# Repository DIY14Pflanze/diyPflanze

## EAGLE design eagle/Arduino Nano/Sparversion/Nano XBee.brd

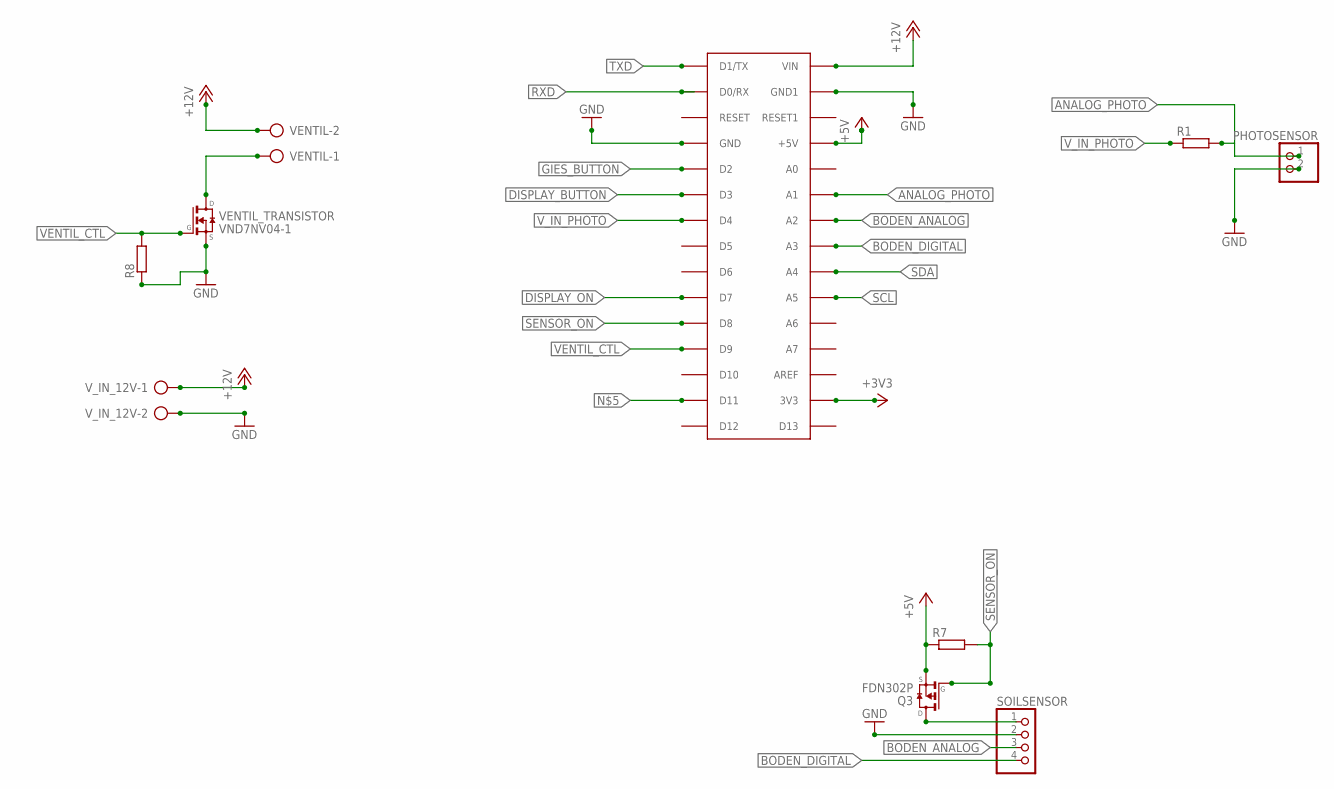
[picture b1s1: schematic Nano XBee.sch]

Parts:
PHOTOSENSOR: PINHD-1X2; 1X02
Q3: FDN302P; SSOT-3
R1: R-EU_0207/7; 0207/7
R7, R8: R-EU_M0805; M0805
SOILSENSOR: PINHD-1X4; 1X04
U$1: ARDUINONANO; PDIP-32
VENTIL: AK500/2
VENTIL_TRANSISTOR: VND7NV04-1; IPAK
V_IN_12V: AK500/2

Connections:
+3V3: U$1.3V3
+5V: Q3.2 (S), R7.1, U$1.+5V
+12V: U$1.VIN, VENTIL.2, V_IN_12V.1
ANALOG_PHOTO: PHOTOSENSOR.1, R1.2, U$1.A1
BODEN_ANALOG: SOILSENSOR.3, U$1.A2
BODEN_DIGITAL: SOILSENSOR.4, U$1.A3
DISPLAY_BUTTON: U$1.D3
DISPLAY_ON: U$1.D7
GIES_BUTTON: U$1.D2
GND: PHOTOSENSOR.2, R8.1, SOILSENSOR.2, U$1.GND, U$1.GND1, VENTIL_TRANSISTOR.3 (S), V_IN_12V.2
unnamed: VENTIL.1, VENTIL_TRANSISTOR.2 (D)
unnamed: Q3.3 (D), SOILSENSOR.1
RXD: U$1.D0/RX
SCL: U$1.A5
SDA: U$1.A4
SENSOR_ON: Q3.1 (G), R7.2, U$1.D8
TXD: U$1.D1/TX
VENTIL_CTL: R8.2, U$1.D9, VENTIL_TRANSISTOR.1 (G)
V_IN_PHOTO: R1.1, U$1.D4

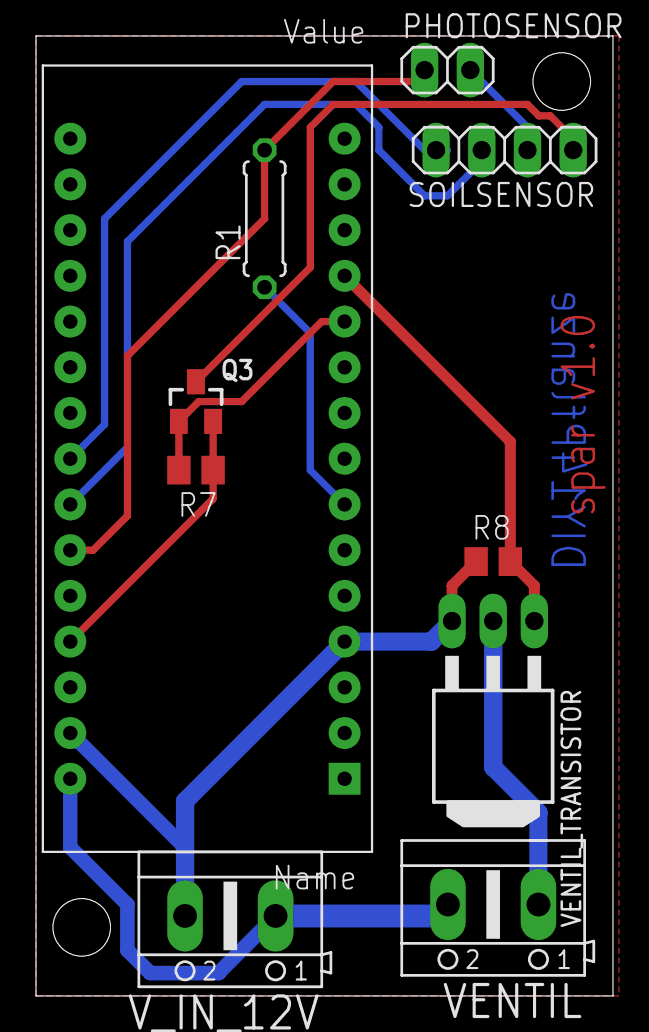
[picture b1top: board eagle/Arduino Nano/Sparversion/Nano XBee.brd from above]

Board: 2 copper layers, 32.1 x 53.3 mm, 10 parts (0 on the bottom side), 11 nets.

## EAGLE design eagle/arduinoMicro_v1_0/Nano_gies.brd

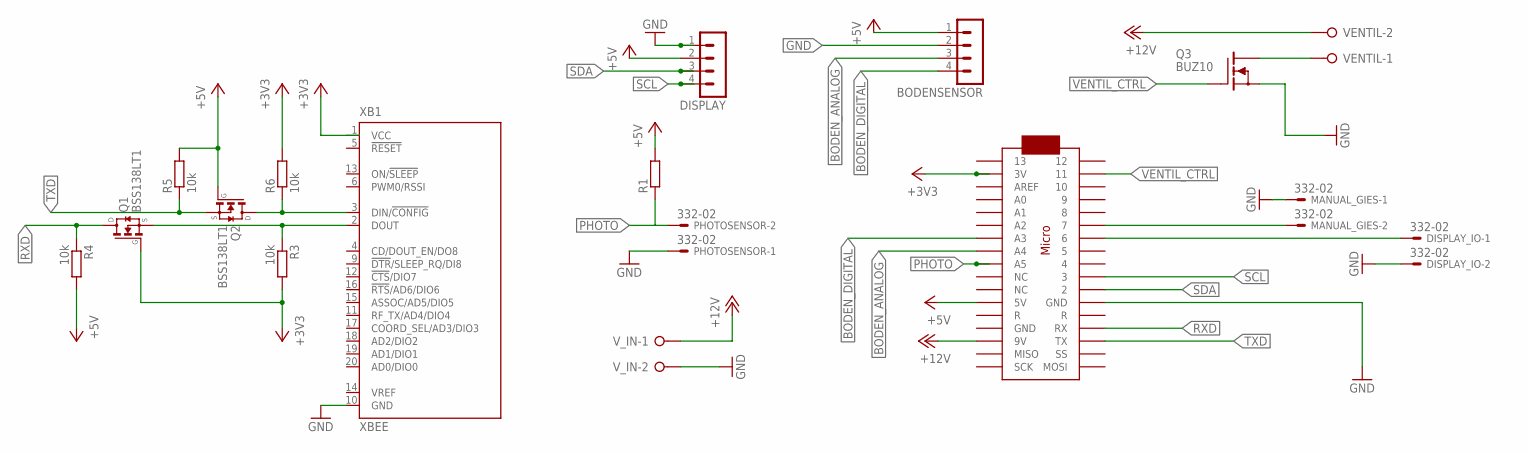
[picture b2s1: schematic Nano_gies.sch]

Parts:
BODENSENSOR: MA04-1
DISPLAY: MA04-1
DISPLAY_IO: 332-02
MANUAL_GIES: 332-02
PHOTOSENSOR: 332-02
Q1, Q2: BSS138LT1; SOT23
Q3: BUZ10; TO220
R1: R-EU_M0805; M0805
R3, R4, R5, R6: 10k; M0805
U$1: ARDUINOMICRO
VENTIL: W237-02P; W237-132
V_IN: W237-02P; W237-132
XB1: XBEE

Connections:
+3V3: Q1.1 (G), R3.2, R6.2, U$1.P$33 (3V), XB1.1 (VCC)
+5V: BODENSENSOR.1, DISPLAY.2, Q2.1 (G), R1.2, R4.2, R5.2, U$1.P$23 (5V)
+12V: U$1.P$20 (9V), VENTIL.2, V_IN.1
BODEN_ANALOG: BODENSENSOR.3, U$1.P$27 (A4)
BODEN_DIGITAL: BODENSENSOR.4, U$1.P$28 (A3)
GND: BODENSENSOR.2, DISPLAY.1, DISPLAY_IO.2, MANUAL_GIES.1, PHOTOSENSOR.1, Q3.3 (S), U$1.P$21 (GND), V_IN.2, XB1.10 (GND)
unnamed: MANUAL_GIES.2, U$1.P$6 (7)
unnamed: Q1.2 (S), R3.1, XB1.2 (DOUT)
unnamed: DISPLAY_IO.1, U$1.P$7 (6)
unnamed: Q3.2 (D), VENTIL.1
unnamed: Q2.3 (D), R6.1, XB1.3 (DIN/!CONFIG)
PHOTO: PHOTOSENSOR.2, R1.1, U$1.P$26 (A5)
RXD: Q1.3 (D), R4.1, U$1.P$14 (RX)
SCL: DISPLAY.4, U$1.P$10 (3)
SDA: DISPLAY.3, U$1.P$11 (2)
TXD: Q2.2 (S), R5.1, U$1.P$15 (TX)
VENTIL_CTRL: Q3.1 (G), U$1.P$2 (11)

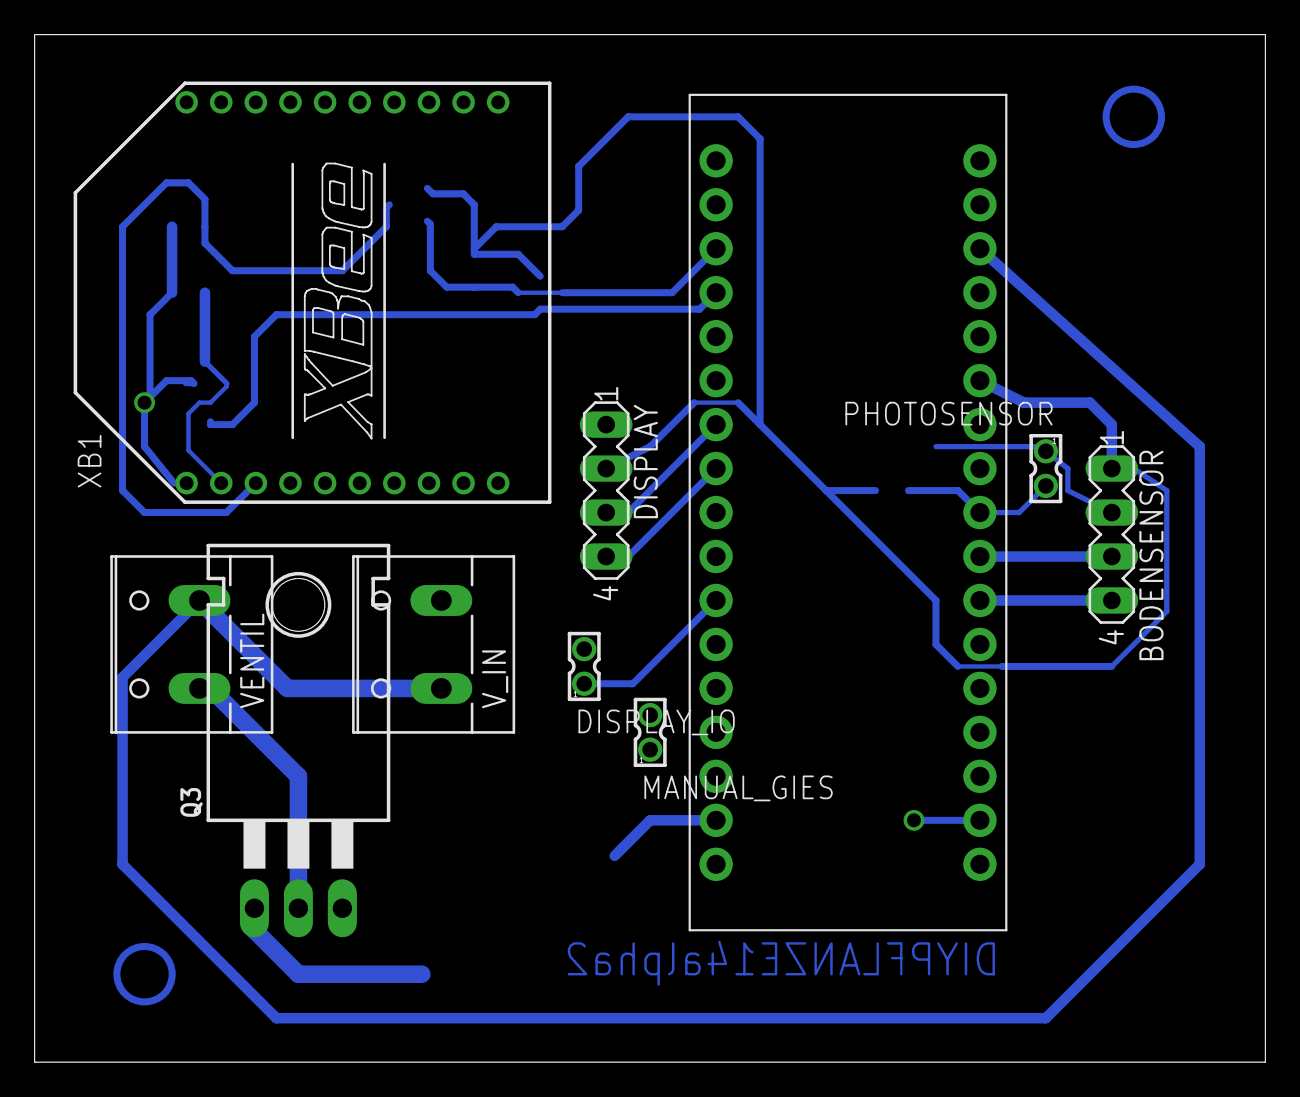
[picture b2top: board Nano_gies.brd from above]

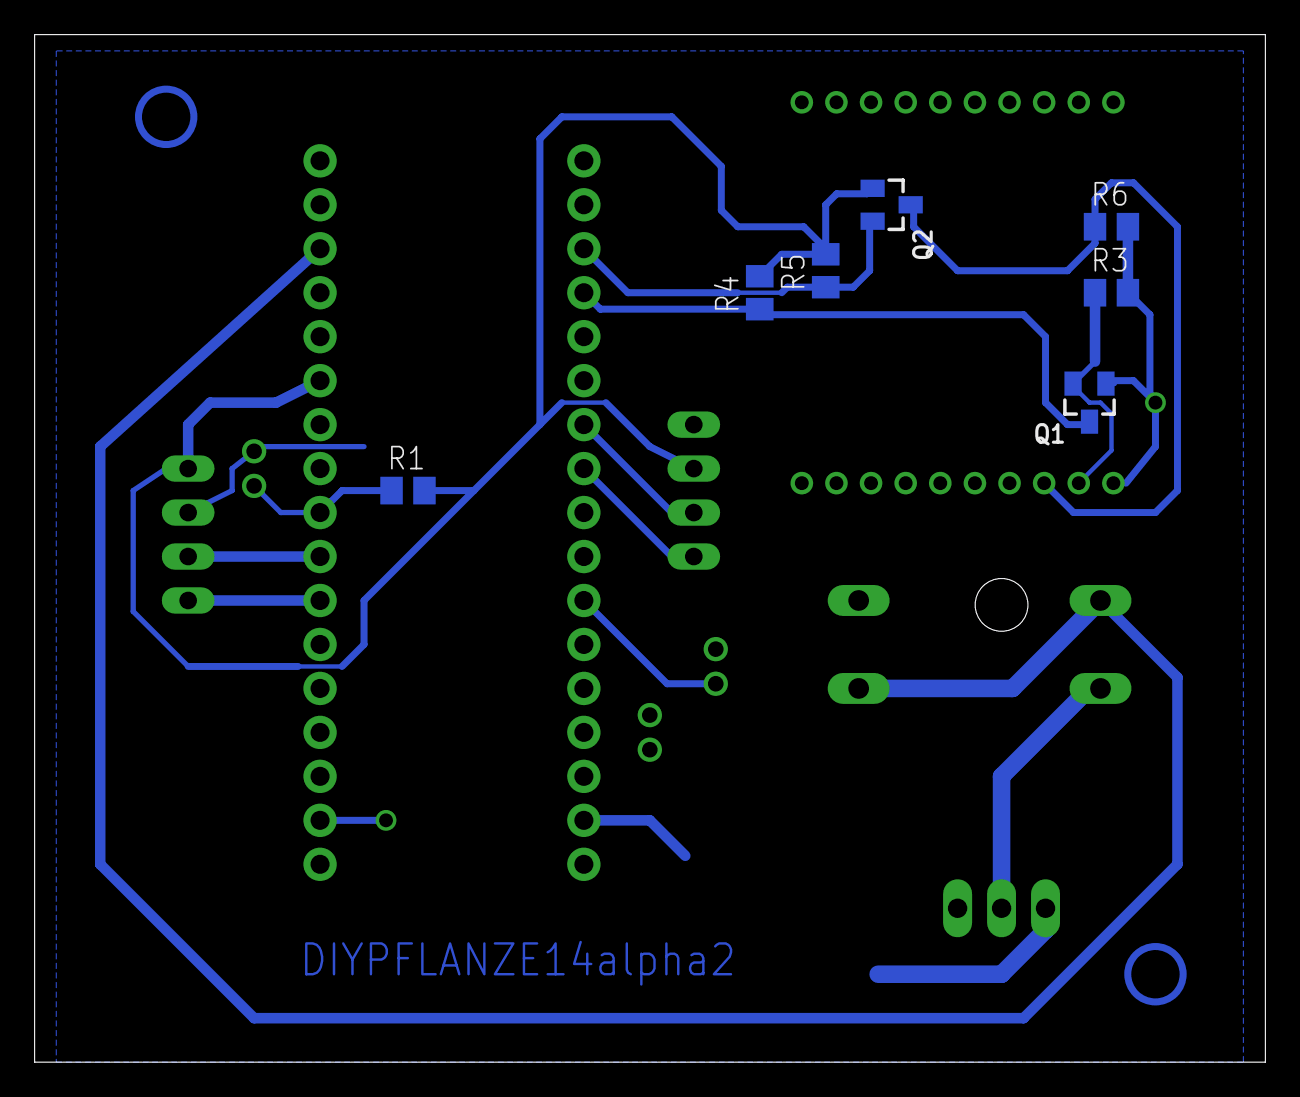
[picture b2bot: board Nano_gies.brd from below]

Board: 2 copper layers, 71.1 x 59.4 mm, 17 parts (7 on the bottom side), 17 nets.

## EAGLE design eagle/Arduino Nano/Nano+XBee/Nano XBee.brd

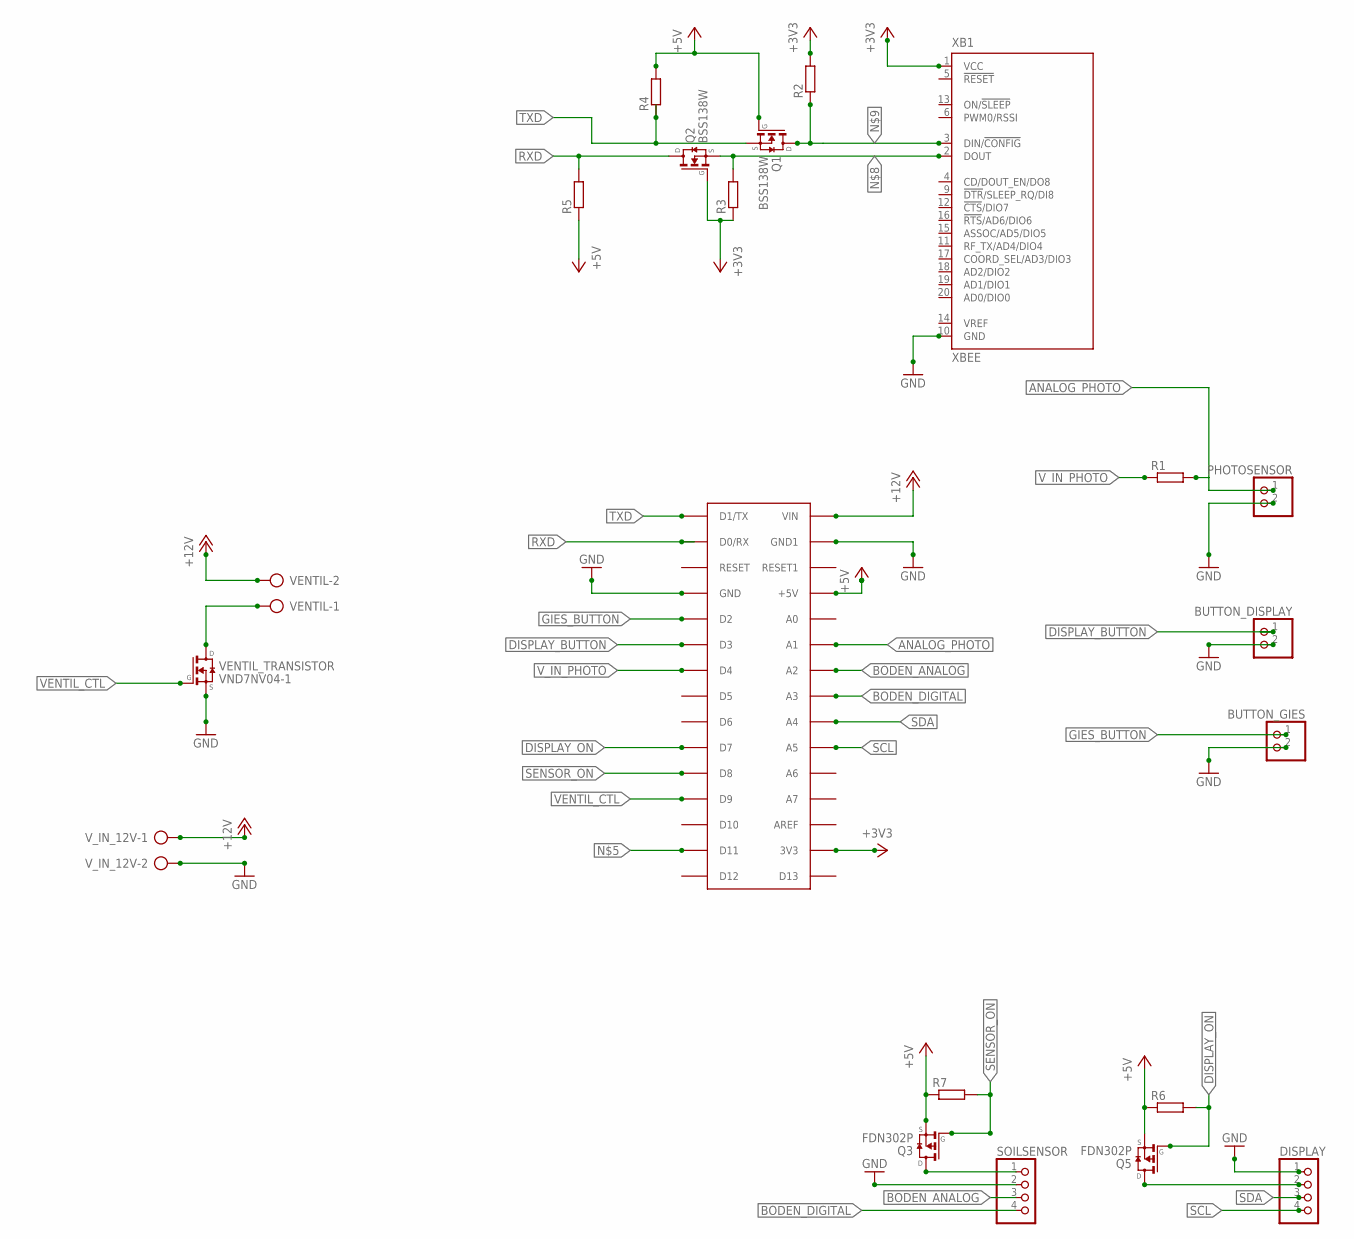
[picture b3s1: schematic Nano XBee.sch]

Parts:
BUTTON_DISPLAY: PINHD-1X2; 1X02
BUTTON_GIES: PINHD-1X2; 1X02
DISPLAY: PINHD-1X4; 1X04
PHOTOSENSOR: PINHD-1X2; 1X02
Q1, Q2: BSS138W; SOT323-R
Q3, Q5: FDN302P; SSOT-3
R1: R-EU_0207/7; 0207/7
R2, R3, R4, R5, R6, R7: R-EU_M0805; M0805
SOILSENSOR: PINHD-1X4; 1X04
U$1: ARDUINONANO; PDIP-32
VENTIL: AK500/2
VENTIL_TRANSISTOR: VND7NV04-1; IPAK
V_IN_12V: AK500/2
XB1: XBEE

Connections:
+3V3: Q2.1 (G), R2.2, R3.1, U$1.3V3, XB1.1 (VCC)
+5V: Q1.1 (G), Q3.2 (S), Q5.2 (S), R4.2, R5.1, R6.1, R7.1, U$1.+5V
+12V: U$1.VIN, VENTIL.2, V_IN_12V.1
ANALOG_PHOTO: PHOTOSENSOR.1, R1.2, U$1.A1
BODEN_ANALOG: SOILSENSOR.3, U$1.A2
BODEN_DIGITAL: SOILSENSOR.4, U$1.A3
DISPLAY_BUTTON: BUTTON_DISPLAY.1, U$1.D3
DISPLAY_ON: Q5.1 (G), R6.2, U$1.D7
GIES_BUTTON: BUTTON_GIES.1, U$1.D2
GND: BUTTON_DISPLAY.2, BUTTON_GIES.2, DISPLAY.1, PHOTOSENSOR.2, SOILSENSOR.2, U$1.GND, U$1.GND1, VENTIL_TRANSISTOR.3 (S), V_IN_12V.2, XB1.10 (GND); also elsewhere on the board
unnamed: DISPLAY.2, Q5.3 (D)
unnamed: VENTIL.1, VENTIL_TRANSISTOR.2 (D)
unnamed: Q3.3 (D), SOILSENSOR.1
unnamed: Q2.2 (S), R3.2, XB1.2 (DOUT)
unnamed: Q1.3 (D), R2.1, XB1.3 (DIN/!CONFIG)
RXD: Q2.3 (D), R5.2, U$1.D0/RX
SCL: DISPLAY.4, U$1.A5
SDA: DISPLAY.3, U$1.A4
SENSOR_ON: Q3.1 (G), R7.2, U$1.D8
TXD: Q1.2 (S), R4.1, U$1.D1/TX
VENTIL_CTL: U$1.D9, VENTIL_TRANSISTOR.1 (G); also elsewhere on the board
V_IN_PHOTO: R1.1, U$1.D4

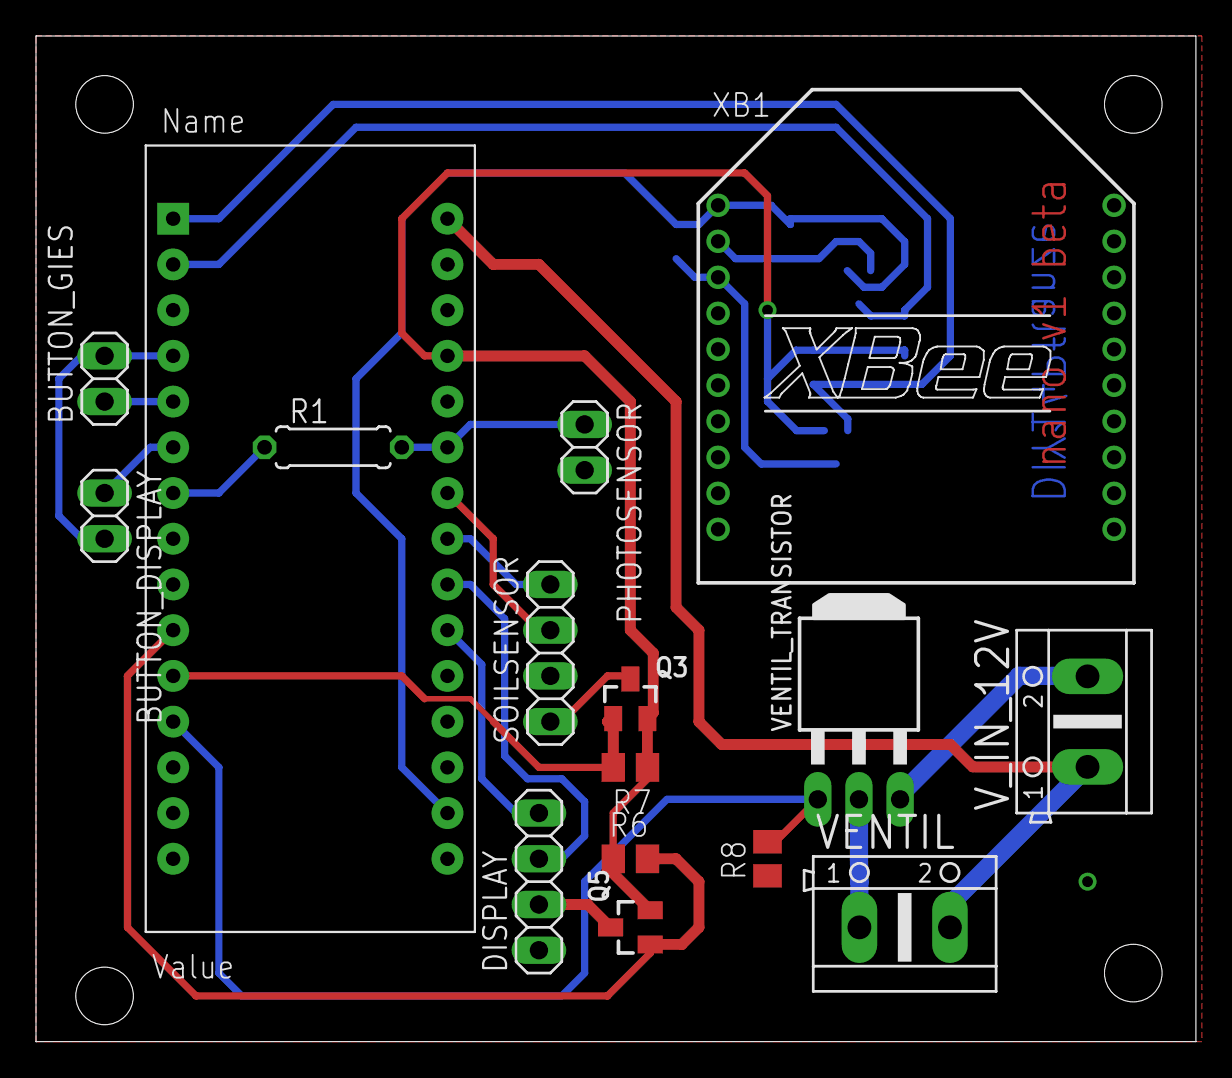
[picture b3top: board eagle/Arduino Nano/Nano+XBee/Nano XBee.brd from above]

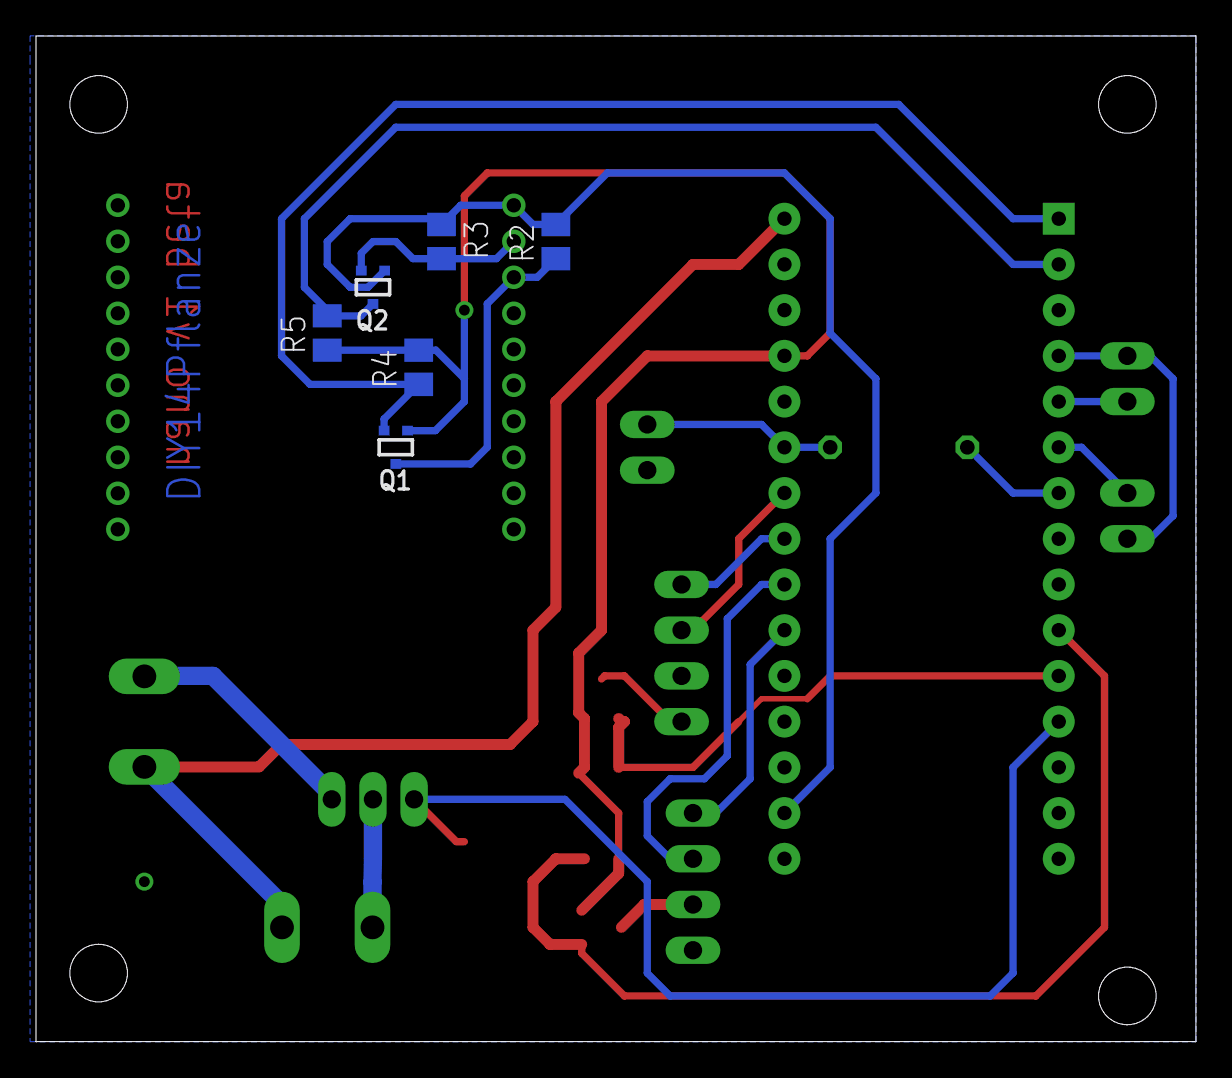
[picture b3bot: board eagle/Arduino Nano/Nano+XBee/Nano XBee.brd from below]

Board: 2 copper layers, 64.4 x 55.9 mm, 22 parts (6 on the bottom side), 22 nets.

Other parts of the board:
R8: M0805

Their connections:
GND: R8.1; also elsewhere on the board
VENTIL_CTL: R8.2; also elsewhere on the board

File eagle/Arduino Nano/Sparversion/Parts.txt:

Partlist

Exported from Nano XBee.sch at 12.02.2015 10:09:27

EAGLE Version 7.0.0 Copyright (c) 1988-2014 CadSoft

Assembly variant: 

Part              Value          Device      Package  Library        Sheet

BUTTON_DISPLAY                   PINHD-1X2   1X02     pinhead        1
BUTTON_GIES                      PINHD-1X2   1X02     pinhead        1
DISPLAY                          PINHD-1X4   1X04     pinhead        1
PHOTOSENSOR                      PINHD-1X2   1X02     pinhead        1
Q1                BSS138W        BSS138W     SOT323-R transistor-fet 1
Q2                BSS138W        BSS138W     SOT323-R transistor-fet 1
Q3                FDN302P        FDN302P     SSOT-3   transistor-fet 1
Q5                FDN302P        FDN302P     SSOT-3   transistor-fet 1
R1                               R-EU_0207/7 0207/7   rcl            1
R2                               R-EU_M0805  M0805    rcl            1
R3                               R-EU_M0805  M0805    rcl            1
R4                               R-EU_M0805  M0805    rcl            1
R5                               R-EU_M0805  M0805    rcl            1
R6                               R-EU_M0805  M0805    rcl            1
R7                               R-EU_M0805  M0805    rcl            1
R8                               R-EU_M0805  M0805    rcl            1
SOILSENSOR                       PINHD-1X4   1X04     pinhead        1
U$1               ARDUINONANO    ARDUINONANO PDIP-32  jet-lib        1
VENTIL                           AK500/2     AK500/2  con-ptr500     1
VENTIL_TRANSISTOR VND7NV04-1     VND7NV04-1  IPAK     transistor-fet 1
V_IN_12V                         AK500/2     AK500/2  con-ptr500     1
XB1               XBEE           XBEE        XBEE     maxstream      1

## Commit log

2014-12-02 lists for things that have been done and should be done
2014-12-02 Moved done.txt and todo.txt to wiki page on gitHub.
2014-12-16 Ordnerhierachie hinzugefuegt fuer Projekt
2015-01-26 erste Doku
2015-01-29 Erste Version vom arduino Programm
2015-02-10 Add: Schaltplan fuer den Arduino Nano mit XBee //Es fehlt noch das Layout
2015-02-11 add: Layout fuer Nano+XBee modified: kleine Aenderung am Schaltplan
2015-02-15 Code fuer Taster erstellt und so umgeschrieben, dass die einstellungen remot geaendert werden koennen.
2015-02-17 +PartList of Nano Layout
2015-02-18 Dokumentation weitergeschrieben
2015-02-20 Abschnitt elektronik hinzugefuegt
2015-02-20 Dokumentation: -title eingefuegt -Sparversion eingefügt -Tabelle geändert -Text produziert
2015-02-20 rm: make aufgeraeumt
2015-02-20 Gehaeuse Plan und Software von Dmitrii
2015-02-20 build Ordner fuer Doku hinzugefügt
2015-02-20 Version 1.0 der Hauptplatine
2015-02-20 Platzhalter für Bilder eingefügt
2015-02-21 Anpassung eagel Files für Grafiken für die Doku. Bilder in Doku eingefügt
2015-02-21 Doku: Abschnitt Kommunikaiton ausgebaut
2015-02-22 Doku: Umstruckturierung wegen Sparversion. Bilder eingefügt. HowTo IEEEtran pdf hinzugefügt
2015-02-22 anpassung der Fehler im Schaltplan beim Anschluss XBee zum Mikrocontroller
2015-02-24 keine Aenderung
2015-02-24 Erweiterung der Dokumentation -Fehlerbeseitigung +Ausweitung des Textes
2015-02-24 Erweiterung der Dokumentation +Sparversion erweitert
2015-02-25 Eagle Sparversion (Layout+Schaltplan) +Schaltplan Sparversion +Layout Sparversion Doku: Sparversion erweitert
2015-02-25 Programm fuer die Sparversion +Einfaches Programm fuer die Sparversion
2015-02-25 Doku aufgeteilt in 3 Dokumente
2015-02-25 Visio Diagramm fuer SV hinzugefuegt.
2015-02-25 Rename SV_Ablaufdiagramm Styleaenderung SV_Ablaufdiagramm
2015-02-25 Erste Korrektur der Doku. Einfügen von Erklärung Pegelwandler
2015-02-25 Sparvesion Bild hinzugefuegt
    Sparvesion Bild hinzugefuegt
2015-02-25 Sparversion Kalibrierung der Sensors eingefügt
2015-02-25 Schemagrafik eingefügt
2015-02-25 Ablaufgrafik für Arduinocode erstellt und in doku eingefügt
2015-02-25 fazit.tex usepackage epstopdf
2015-02-25 Kapitel Programm für Arduino Version ausformuliert. Neues Packet eingefügt für Code-Teile
2015-02-25 Namensaenderung wegen Atmelstudio Programmierer
2015-02-25 Sechs Seiten Dokumentation: fazit.tex: Weiterentwicklung hinzugefügt arduinoVariante.tex: Schaltplan verschoben Bilder (SV_Ablaufplan, Schaltplan) etwas verkleinert Warnings reduziert
2015-02-26 Fehlerverbesserung der Doku
2015-02-26 Doku Verbesserungen im pdf
2015-02-26 Doku: Noch mehr Kommas gesetzt und Rechtschreibung
2015-02-26 Änderungen von Christoph eingearbeitet. Bildpositionierung angepasst um 6-Seiten grenze zu halten.
2015-02-26 Anpassung in Fazit. Abschnitt über cmdTool auskommentiert
2015-02-26 Letzte Korrektur. Fehler in Bild 7 korregiert. Abschnitt Konfigurationstool wieder eingefügt
